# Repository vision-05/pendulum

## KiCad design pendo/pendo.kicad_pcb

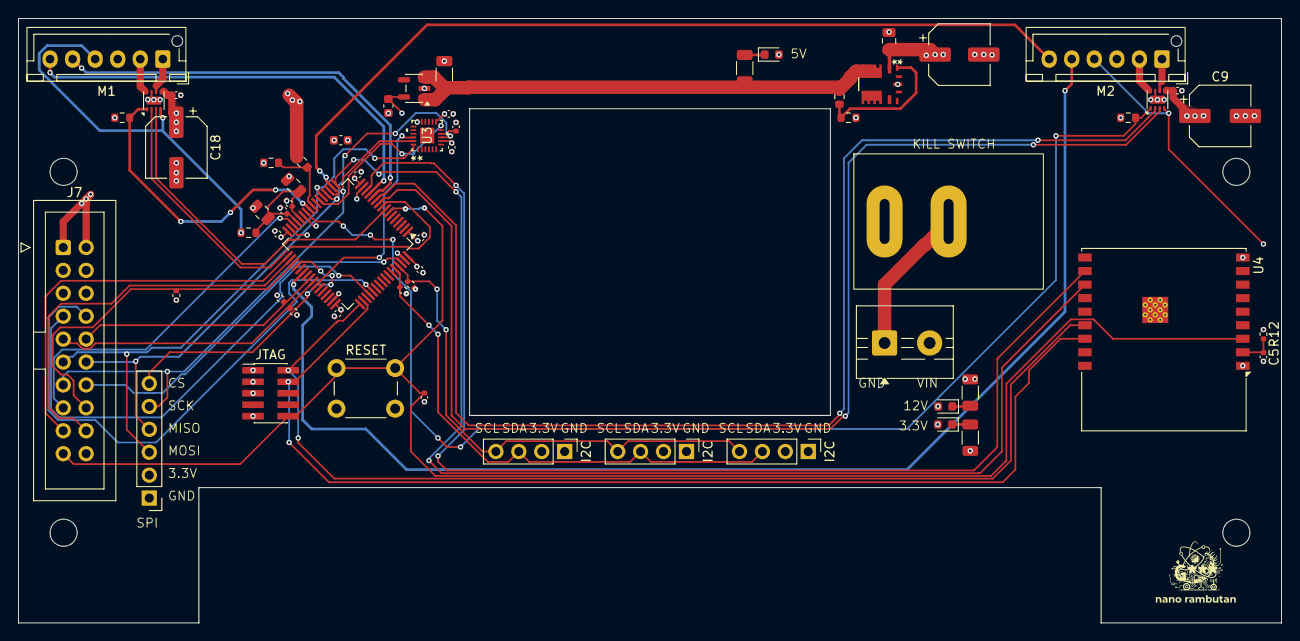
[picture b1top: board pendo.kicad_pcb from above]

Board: 4 copper layers, 140.0 x 67.0 mm, 60 parts (0 on the bottom side), 49 nets.

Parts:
C1, C2, C3, C4, C5, C6, C10, C11, C20, C22, C24: 1u; C_0402_1005Metric
C7: 10u; C_0603_1608Metric
C8, C23: 0.1u; C_0402_1005Metric
C9, C18: 47u; CP_Elec_6.3x5.4
C12: 1u; C_0603_1608Metric
C13: 1u; C_1206_3216Metric
C14, C19, C21: 10u; C_0805_2012Metric
C15: 100u; CP_Elec_6.3x7.7
C25: 10n; C_0402_1005Metric
D1, D2, D3: LED; LED_0603_1608Metric
FB1: FerriteBead_Small; R_0603_1608Metric
I2C, I2C#2, I2C#3: Conn_01x04_Pin; PinHeader_1x04_P2.54mm_Vertical
J1: Screw_Terminal_01x02; TerminalBlock_MaiXu_MX126-5.0-02P_1x02_P5.00mm
J7: Conn_02x10_Odd_Even; IDC-Header_2x10_P2.54mm_Vertical
J10: Conn_01x06_Pin; PinHeader_1x06_P2.54mm_Vertical
JTAG: Conn_ARM_JTAG_SWD_10; PinHeader_2x05_P1.27mm_Vertical_SMD
M1, M2: Conn_01x06_Pin; JST_XH_B6B-XH-AM_1x06_P2.50mm_Vertical
R1, R2: 1.5k; R_0603_1608Metric
R3, R4: 10k; R_0603_1608Metric
R5: 3.3k; R_0603_1608Metric
R6: 1.37k; R_0603_1608Metric
R7, R12: 10k; R_0402_1005Metric
R8, R9, R10, R11: 4.7k; R_0402_1005Metric
R13: 1k; R_1206_3216Metric
R14: 300; R_1206_3216Metric
R15: 120; R_1206_3216Metric
RESET: SW_Push; SW_PUSH_6mm
SW2: SW_SPST; SWITCH HIGH VOLTAGE
U1: STM32G431RBTx; LQFP-64_10x10mm_P0.5mm
U3: MPU-6500; QFN24_3X3X0P9_IVS
U4: ESP32-C3-WROOM-02
U5: AP2112K-3.3; SOT-23-5
U9: RPX-2.5-CT; RPX-2.5
U10, U11: DRV8231ADSG; WSON-8-1EP_2x2mm_P0.5mm_EP0.9x1.6mm

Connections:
+3.3V: C1.2, C2.2, C3.2, C4.2, C6.2, C7.1, C12.1, C24.1, C25.1, FB1.2, I2C.2, I2C#2.2, I2C#3.2, J7.5, J10.2, JTAG.1 (VTref), M1.4, M2.4, R7.1, R8.1, R9.1, R10.1, R11.1, R12.1, R15.1, U1.1 (VBAT), U1.16 (VDD), U1.32 (VDD), U1.48 (VDD), U1.64 (VDD), U3.8 (VDDIO), U3.13 (VDD), U4.1 (3V3), U5.5 (VOUT), U10.4 (VREF), U11.4 (VREF)
+3.3VA: C19.1, C20.1, C21.1, C22.1, FB1.1, U1.28 (VREF+), U1.29 (VDDA)
+5V: C13.1, R4.2, R14.1, U5.1 (VIN), U5.3 (EN), U9.3 (VOUT)
+12V: C9.1, C10.2, C11.2, C14.1, C15.1, C18.1, J7.1, J7.2, R3.1, R13.1, SW2.1 (A), U9.2 (VIN), U10.5 (VM), U11.5 (VM)
/ENC1A: M1.5, U1.12 (TIM2_CH1)
/ENC1B: M1.6, U1.13 (TIM2_CH2)
/ENC2A: M2.5, U1.38 (TIM3_CH1)
/ENC2B: M2.6, U1.18 (TIM3_CH2)
/ENC_CS: J10.6, U1.36 (PB14)
/ESP32_RX: U1.14 (USART2_TX), U4.11 (IO20/RXD)
/ESP32_TX: U1.17 (USART2_RX), U4.12 (IO21/TXD)
/E_STOP: J7.16, R7.2, U1.35 (PB13)
/I2C1_SCL: I2C.4, I2C#2.4, I2C#3.4, R10.2, U1.61 (I2C1_SCL)
/I2C1_SDA: I2C.3, I2C#2.3, I2C#3.3, R11.2, U1.60 (I2C1_SDA)
/I2C3_SCL: J7.10, R8.2, U1.40 (I2C3_SCL)
/I2C3_SDA: J7.9, R9.2, U1.41 (I2C3_SDA)
/IMU_CS: U1.42 (PA8), U3.22 (nCS)
/IMU_INT: U1.22 (PC4), U3.12 (INT)
/JDB_RESET: C8.1, J7.19, JTAG.10 (~RESET), RESET.1, U1.7 (PG10), U4.3 (IO4)
/JDB_SWCLK: JTAG.4 (SWCLK/TCK), U1.50 (SYS_JTCK-SWCLK), U4.16 (IO2)
/JDB_SWDIO: JTAG.2 (SWDIO/TMS), U1.49 (SYS_JTMS-SWDIO), U4.15 (IO3)
/M1+: M1.1, U10.6 (OUT1)
/M1-: M1.2, U10.8 (OUT2)
/M2+: M2.1, U11.6 (OUT1)
/M2-: M2.2, U11.8 (OUT2)
/PB11: J7.17, U1.33 (PB11)
/PB12: J7.18, U1.34 (PB12)
/SPI1_GP_CS1: J7.14, U1.62 (PB9)
/SPI1_GP_CS2: J7.15, U1.30 (PB10)
/SPI1_MISO: J7.12, J10.4, U1.20 (SPI1_MISO), U3.9 (SDO/ADO)
/SPI1_MOSI: J7.11, J10.3, U1.21 (SPI1_MOSI), U3.24 (SDA/SDI)
/SPI1_SCK: J7.13, J10.5, U1.19 (SPI1_SCK), U3.23 (SCL/SCLK)
/TIM1_1: U1.8 (TIM1_CH1), U10.3 (IN1)
/TIM1_2: U1.9 (TIM1_CH2), U10.2 (IN2)
/TIM1_3: U1.10 (TIM1_CH3), U11.3 (IN1)
/TIM1_4: U1.11 (TIM1_CH4), U11.2 (IN2)
/USART3_RX: J7.8, U1.53 (USART3_RX)
/USART3_TX: J7.7, U1.52 (USART3_TX)
/VBAT_PROTECT: R3.2, R5.1, U1.24 (ADC1_IN15)
/VPROPI1: R1.2, U1.25 (ADC1_IN12), U10.1 (IPROPI)
/VPROPI2: R2.2, U1.26 (ADC2_IN12), U11.1 (IPROPI)
GND: C1.1, C2.1, C3.1, C4.1, C5.2, C6.1, C7.2, C8.2, C9.2, C10.1, C11.1, C12.2, C13.2, C14.2, C15.2, C18.2, C19.2, C20.2, C21.2, C22.2, C23.2, C24.2, C25.2, D1.2 (A), D2.2 (A), D3.2 (A), I2C.1, I2C#2.1, I2C#3.1, J1.2, J7.3, J7.4, J7.6, J7.20, J10.1, JTAG.3 (GND), JTAG.5 (GND), JTAG.9 (GNDDetect), M1.3, M2.3, R1.1, R2.1, R5.2, R6.2, RESET.2, U1.15 (VSS), U1.27 (VSSA), U1.31 (VSS), U1.47 (VSS), U1.63 (VSS), U3.18 (GND), U4.9 (GND), U4.19 (GND), U5.2 (GND), U9.8 (GND), U10.7 (GND), U10.9 (GND), U11.7 (GND), U11.9 (GND)
unnamed: D1.1 (K), R13.2
unnamed: D2.1 (K), R14.2
unnamed: D3.1 (K), R15.2
unnamed: J1.1, SW2.2 (B)
unnamed: C23.1, U3.10 (REGOUT)
unnamed: C5.1, R12.2, U4.2 (EN)
unnamed: R4.1, R6.1, U9.1 (FB)

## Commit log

2026-03-25 added initial schematic
2026-03-26 added caps and resistor values
2026-03-27 adding i2c
2026-03-29 plane pours
2026-04-20 started gerber redesign + update power components
2026-04-22 cleaning up pendulum schematic
2026-04-22 cleaned up schematic
2026-04-22 finished schematic
2026-04-25 added planes and almost finished routing
2026-04-25 kicad pro
2026-04-25 more routing
2026-04-28 final production ready PCB complete with BOM and POS
